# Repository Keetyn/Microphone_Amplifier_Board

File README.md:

# Microphone_Amplifier_Board

This is an audio amplifier board capable of taking any small audio signal, differential or singled ended and amplifying it to an output of 30W @ 8 ohms. This was designed, built, and tested as more of an educational exercise than anything else and thus relies on screw terminal inputs for power and requires external power supplies. This is a 4-layer board with the two inner copper layers being used as Ground planes.

The board can be thought of as having four distinct sections:

1. the first is a THAT 1510 instrumentation amplifier with a tunable gain that is meant to take in a signal       from either a microphone or an aux cord. This amplifies the signal by a gain of anywhere from +32 - +62dB      depending on the position of the gain potentiometer. This input can accept a differential or single    
   ended input.
2. The second is the EQ filter. This is a state variable topology filter. This implementation provides         
   potentiometers that allow the user to adjust the damping (alpha), Center Frequency (Fo), Gain (A), and a 
   latching pushbutton that can enable or disable the filter. Fo can be adjusted from 300Hz - 2.2kHz.             alpha can be adjusted from 0.5 - 10. Gain can be adjusted from -40dB - +15dB
3. The third is a Peak Limiter using a THAT 4305 Compander IC. This is a versatile analog processing IC that with the accompanying circuitry and potentiometers acts as a non-distorting peak limiter with the ability to adjust the compression threshold and compression ratio. The threshold can be adjusted from +7.3dBV - +9.74dBV. The compression ratio can also be adjusted anywhere from infinity:1 to a value approaching 1:1.
4. THe final section of this board is a TPA3122 Class-D analog input power amplifier. This IC is capable of outputting 30W and has an accompanying potentiometer that can be used to attenuate its input as a volume control.

Each of the above listed sections is split apart by 100 mil pin headers that completely break any connection between the sections. This was done for easier test and troubleshooting and to help compartmentalize individual portions of the board. Below is a screenshot of a 3D render of the board in KiCad with each section clearly separate with silkscreen lines and labels.

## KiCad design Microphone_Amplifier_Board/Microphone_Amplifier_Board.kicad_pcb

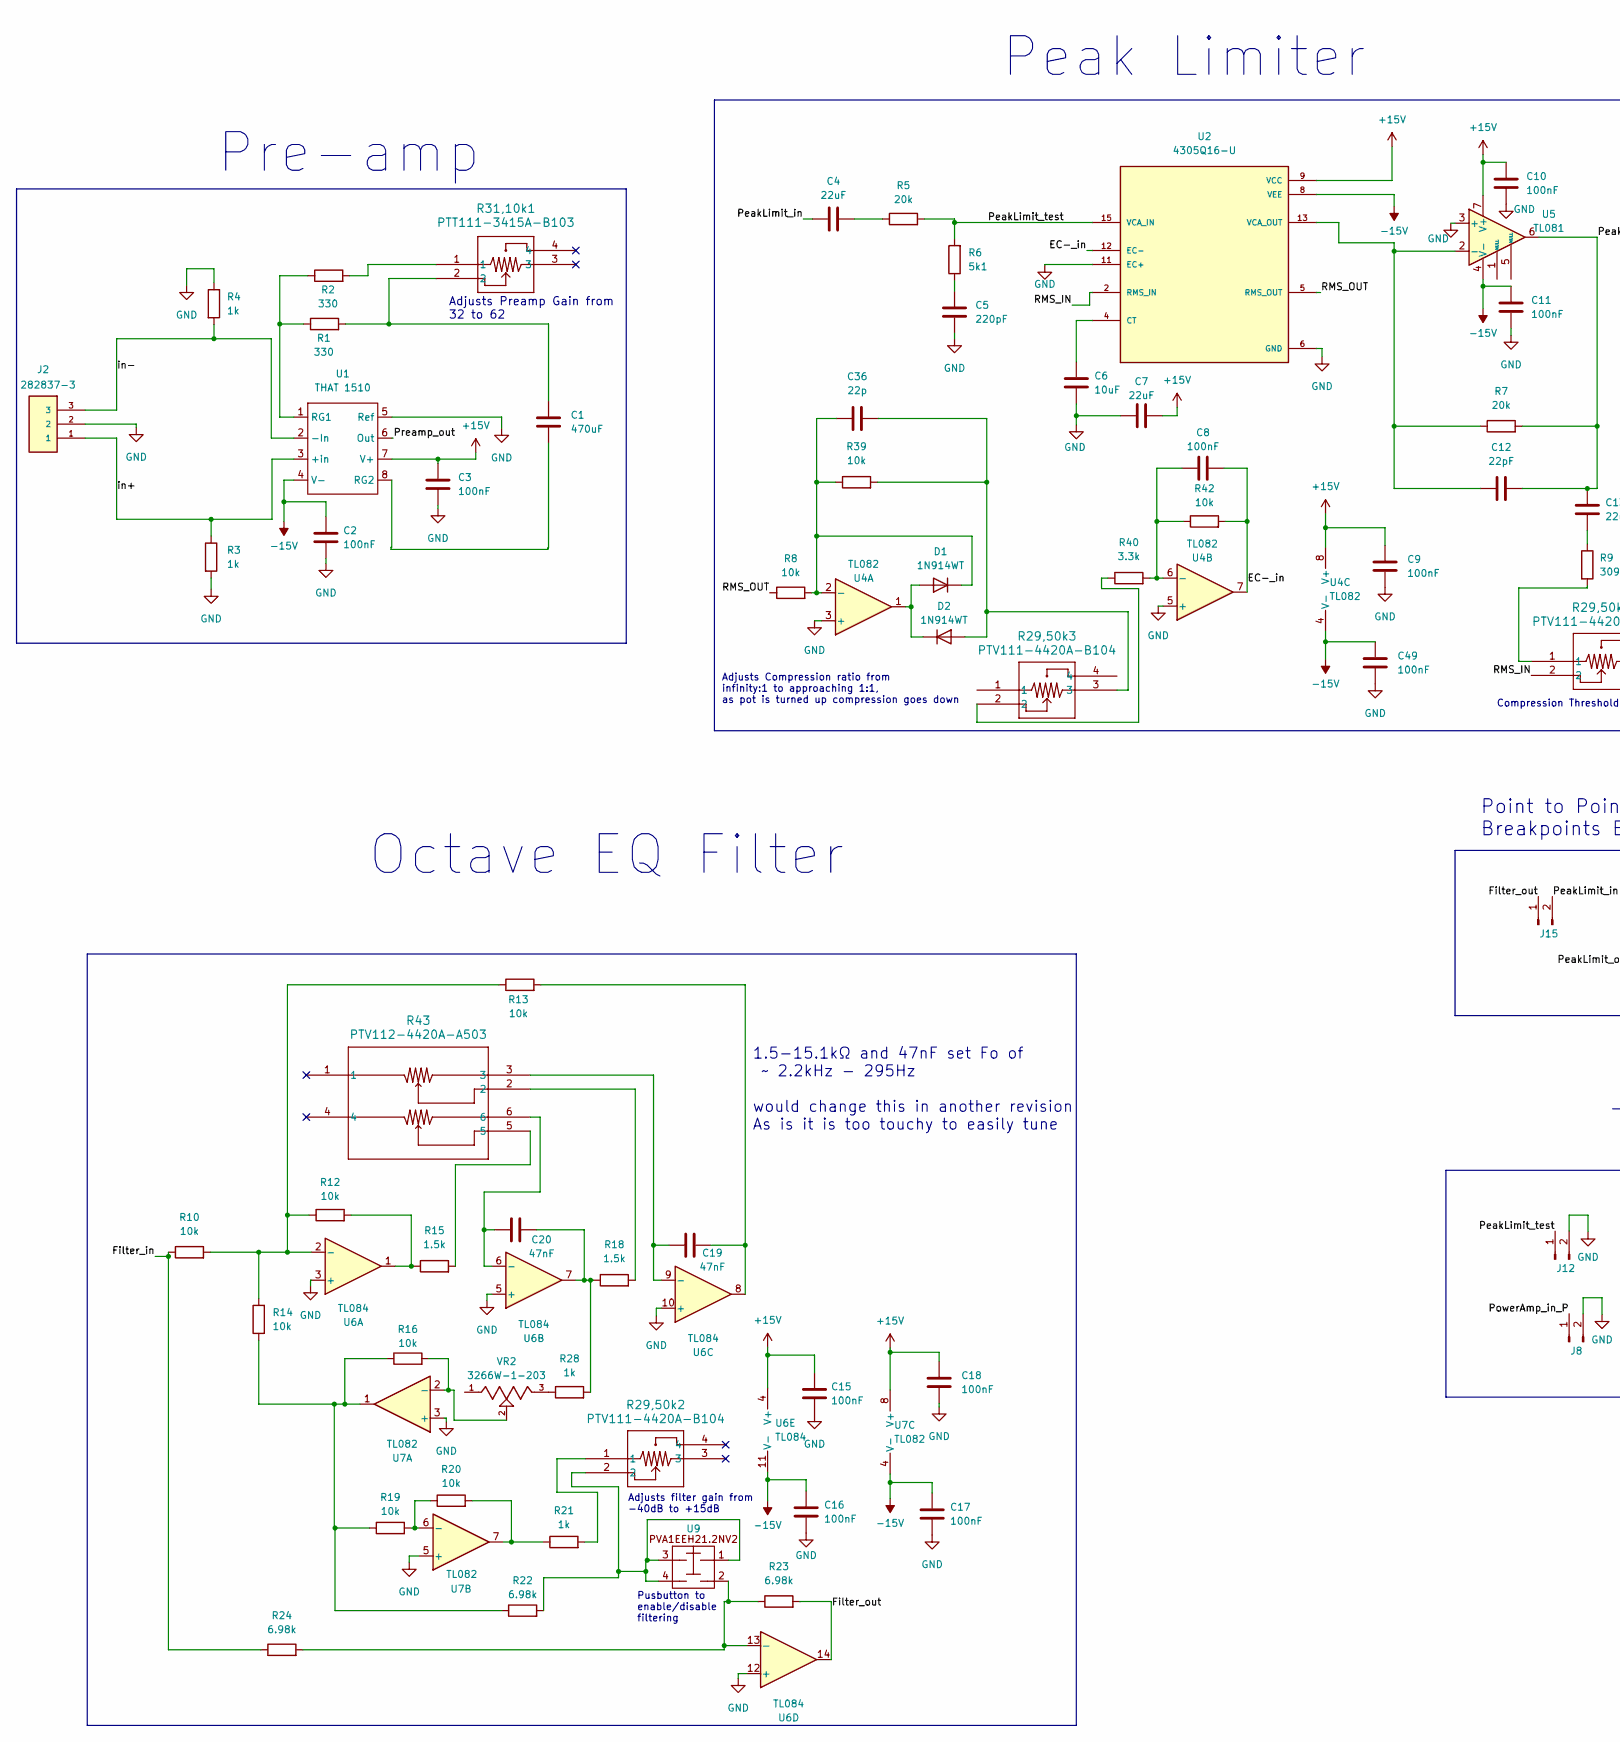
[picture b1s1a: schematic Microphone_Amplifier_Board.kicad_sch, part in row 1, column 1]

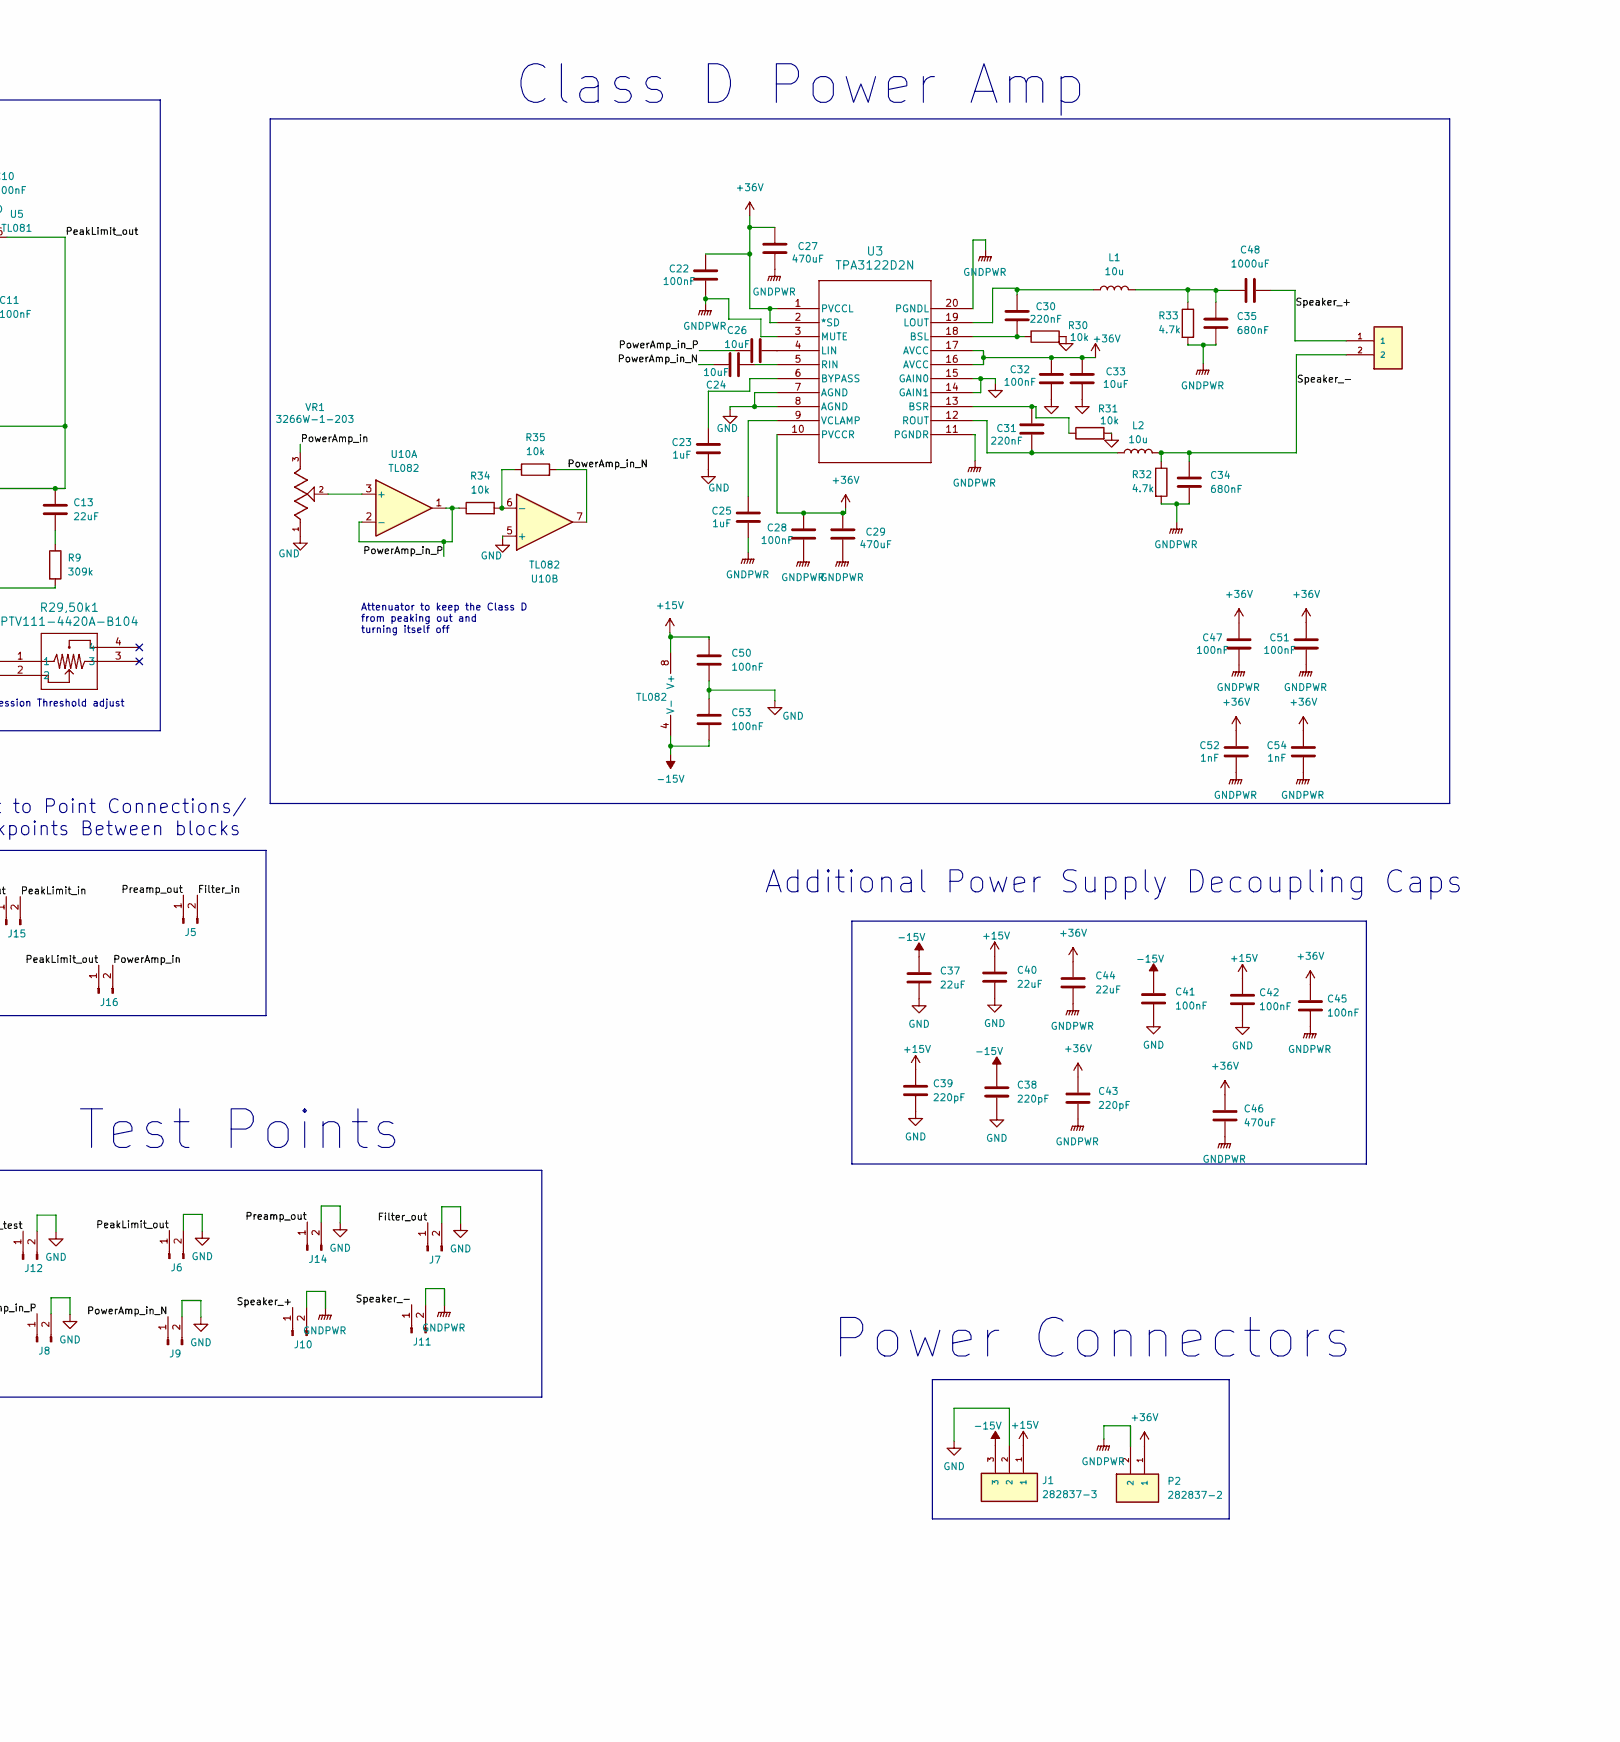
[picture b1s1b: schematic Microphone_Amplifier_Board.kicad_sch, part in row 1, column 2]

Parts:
C1, C27, C29, C46: 470uF; CP_Radial_D13.0mm_P5.00mm
C2, C3, C8, C9, C10, C11, C15, C16, C17, C18, C22, C28, C32, C41, C42, C45, C47, C49, C50, C51, C53: 100nF; C_1206_3216Metric_Pad1.33x1.80mm_HandSolder
C4, C7, C13, C37, C40, C44: 22uF; C_1206_3216Metric_Pad1.33x1.80mm_HandSolder
C5, C38, C39, C43: 220pF; C_1206_3216Metric_Pad1.33x1.80mm_HandSolder
C6, C24, C26, C33: 10uF; C_1206_3216Metric_Pad1.33x1.80mm_HandSolder
C12: 22pF; C_1206_3216Metric_Pad1.33x1.80mm_HandSolder
C19, C20: 47nF; C_1206_3216Metric_Pad1.33x1.80mm_HandSolder
C23, C25: 1uF; C_1206_3216Metric_Pad1.33x1.80mm_HandSolder
C30, C31: 220nF; C_1206_3216Metric_Pad1.33x1.80mm_HandSolder
C34, C35: 680nF; C_1206_3216Metric_Pad1.33x1.80mm_HandSolder
C36: 22p; C_1206_3216Metric_Pad1.33x1.80mm_HandSolder
C48: 1000uF; CP_Radial_D13.0mm_P5.00mm
C52, C54: 1nF; C_1206_3216Metric_Pad1.33x1.80mm_HandSolder
D1, D2: 1N914WT; D_SOD-523
J1, J2: 282837-3; TE_282837-3; PARTREV H; DigiKey_Part_Number A113321-ND
J5, J6, J7, J8, J9, J10, J11, J12, J14, J15, J16: Conn_01x02_Pin; PinHeader_1x02_P2.54mm_Vertical
L1, L2: 10u; Power Inductor 10uH
P1, P2: 282837-2; TE_282837-2; PARTREV G3; DigiKey_Part_Number A113320-ND
R1, R2: 330; R_1206_3216Metric_Pad1.30x1.75mm_HandSolder
R3, R4, R21, R28: 1k; R_1206_3216Metric_Pad1.30x1.75mm_HandSolder
R5, R7: 20k; R_1206_3216Metric_Pad1.30x1.75mm_HandSolder
R6: 5k1; R_1206_3216Metric_Pad1.30x1.75mm_HandSolder
R8, R10, R12, R13, R14, R16, R19, R20, R30, R31, R34, R35, R39, R42: 10k; R_1206_3216Metric_Pad1.30x1.75mm_HandSolder
R9: 309k; R_1206_3216Metric_Pad1.30x1.75mm_HandSolder
R15, R18: 1.5k; R_1206_3216Metric_Pad1.30x1.75mm_HandSolder
R22, R23, R24: 6.98k; R_1206_3216Metric_Pad1.30x1.75mm_HandSolder
R29,50k1, R29,50k2, R29,50k3: PTV111-4420A-B104; PTT111-3_17_BRN
R31,10k1: PTT111-3415A-B103; PTT111-3_17_BRN
R32, R33: 4.7k; R_1206_3216Metric_Pad1.30x1.75mm_HandSolder
R40: 3.3k; R_1206_3216Metric_Pad1.30x1.75mm_HandSolder
R43: PTV112-4420A-A503; PTV112-4_BRN
U1: THAT 1510
U2: 4305Q16-U; PARTREV 10
U3: TPA3122D2N; N20
U4, U7: TL082
U5: TL081
U6: TL084
U9: (no value)
U10: TL082; TL081 SOIC-8
VR1, VR2: 3266W-1-203; TRIM_3266W-1-203

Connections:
+15V: C3.1, C7.2, C9.2, C10.1, C15.1, C18.1, C39.1, C40.1, C42.1, C50.1, J1.1, U1.7 (V+), U2.9 (VCC), U4.8 (V+), U5.7 (V+), U6.4 (V+), U7.8 (V+), U10.8 (V+)
+36V: C22.1, C27.1, C28.1, C29.1, C32.1, C33.1, C43.1, C44.1, C45.1, C46.1, C47.1, C51.1, C52.1, C54.1, P2.1, U3.1 (PVCCL), U3.2 (*SD), U3.10 (PVCCR), U3.16 (AVCC), U3.17 (AVCC)
-15V: C2.1, C11.1, C16.1, C17.1, C37.1, C38.1, C41.1, C49.2, C53.2, J1.3, U1.4 (V-), U2.8 (VEE), U4.4 (V-), U5.4 (V-), U6.11 (V-), U7.4 (V-), U10.4 (V-)
/EC-_in: C8.2, R42.2, U2.12 (EC-), U4.7
/Filter_in: J5.2, R10.1, R24.1
/Filter_out: J7.1, J15.1, R23.2, U6.14
/PeakLimit_in: C4.1, J15.2
/PeakLimit_out: C12.2, C13.1, J6.1, J16.1, R7.2, U5.6
/PeakLimit_test: J12.1, R5.2, R6.2, U2.15 (VCA_IN)
/PowerAmp_in: J16.2, VR1.3
/PowerAmp_in_N: C24.2, J9.1, R35.2, U10.7
/PowerAmp_in_P: C26.2, J8.1, R34.1, U10.1, U10.2 (-)
/Preamp_out: J5.1, J14.1, U1.6 (Out)
/RMS_IN: R29,50k1.2, U2.2 (RMS_IN)
/RMS_OUT: R8.1, U2.5 (RMS_OUT)
/Speaker_+: C48.2, J10.1, P1.1
/Speaker_-: C34.1, J11.1, L2.2, P1.2, R32.1
/in+: J2.1, R3.1, U1.3 (+in)
/in-: J2.3, R4.2, U1.2 (-In)
GND: C2.2, C3.2, C5.2, C6.2, C7.1, C9.1, C10.2, C11.2, C15.2, C16.2, C17.2, C18.2, C23.2, C32.2, C33.2, C37.2, C38.2, C39.2, C40.2, C41.2, C42.2, C49.1, C50.2, C53.1, J1.2, J2.2, J6.2, J7.2, J8.2, J9.2, J12.2, J14.2, R3.2, R4.1, R30.2, R31.2, U1.5 (Ref), U2.6 (GND), U2.11 (EC+), U3.7 (AGND), U3.8 (AGND), U3.14 (GAIN1), U3.15 (GAIN0), U4.3 (+), U4.5 (+), U5.3 (+), U6.3 (+), U6.5 (+), U6.10 (+), U6.12 (+), U7.3 (+), U7.5 (+), U10.5 (+), VR1.1
GNDPWR: C22.2, C25.2, C27.2, C28.2, C29.2, C34.2, C35.2, C43.2, C44.2, C45.2, C46.2, C47.2, C51.2, C52.2, C54.2, J10.2, J11.2, P2.2, R32.2, R33.2, U3.3 (MUTE), U3.11 (PGNDR), U3.20 (PGNDL)
unnamed: C1.1, R1.2, R31,10k1.2
unnamed: C4.2, R5.1
unnamed: C5.1, R6.1
unnamed: C13.2, R9.1
unnamed: C19.2, R13.2, U6.8
unnamed: C20.2, R18.1, R28.2, U6.7
unnamed: C35.1, C48.1, L1.2, R33.1
unnamed: D1.2 (A), D2.1 (K), U4.1
unnamed: C36.1, D1.1 (K), R8.2, R39.1, U4.2 (-)
unnamed: C36.2, D2.2 (A), R29,50k3.3, R39.2
unnamed: R2.2, R31,10k1.1
unnamed: R12.2, R15.1, U6.1
unnamed: R14.1, R16.1, R19.1, R22.1, U7.1
unnamed: R15.2, R43.5
unnamed: R18.2, R43.2
unnamed: R20.2, R21.1, U7.7
unnamed: R21.2, R29,50k2.1
unnamed: R22.2, R29,50k2.2, U9.1, U9.3, U9.4
unnamed: R28.1, VR2.3
unnamed: R9.2, R29,50k1.1
unnamed: R29,50k3.2, R40.1
unnamed: R1.1, R2.1, U1.1 (RG1)
unnamed: C1.2, U1.8 (RG2)
unnamed: C6.1, U2.4 (CT)
unnamed: C12.1, R7.1, U2.13 (VCA_OUT), U5.2 (-)
unnamed: C30.2, R30.1, U3.18 (BSL)
unnamed: C31.1, R31.1, U3.13 (BSR)
unnamed: C23.1, U3.6 (BYPASS)
unnamed: C26.1, U3.4 (LIN)
unnamed: C30.1, L1.1, U3.19 (LOUT)
unnamed: C24.1, U3.5 (RIN)
unnamed: C31.2, L2.1, U3.12 (ROUT)
unnamed: C25.1, U3.9 (VCLAMP)
unnamed: C8.1, R40.2, R42.1, U4.6 (-)
unnamed: R10.2, R12.1, R13.1, R14.2, U6.2 (-)
unnamed: C20.1, R43.6, U6.6 (-)
unnamed: C19.1, R43.3, U6.9 (-)
unnamed: R23.1, R24.2, U6.13 (-), U9.2
unnamed: R16.2, U7.2 (-), VR2.2
unnamed: R19.2, R20.1, U7.6 (-)
unnamed: U10.3 (+), VR1.2
unnamed: R34.2, R35.1, U10.6 (-)

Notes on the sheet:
Pusbutton to enable/disable filtering
Compression Threshold adjust
Adjusts filter gain from -40dB to +15dB
Test Points
Peak Limiter
Class D Power Amp
Power Connectors
Additional Power Supply Decoupling Caps
Octave EQ Filter
Attenuator to keep the Class D from peaking out and turning itself off
Point to Point Connections/ Breakpoints Between blocks
Adjusts Compression ratio from infinity:1 to approaching 1:1, as pot is turned up compression goes down
1.5-15.1kΩ and 47nF set Fo of ~ 2.2kHz - 295Hz would change this in another revision As is it is too touchy to easily tune
Adjusts Preamp Gain from 32 to 62
Pre-amp

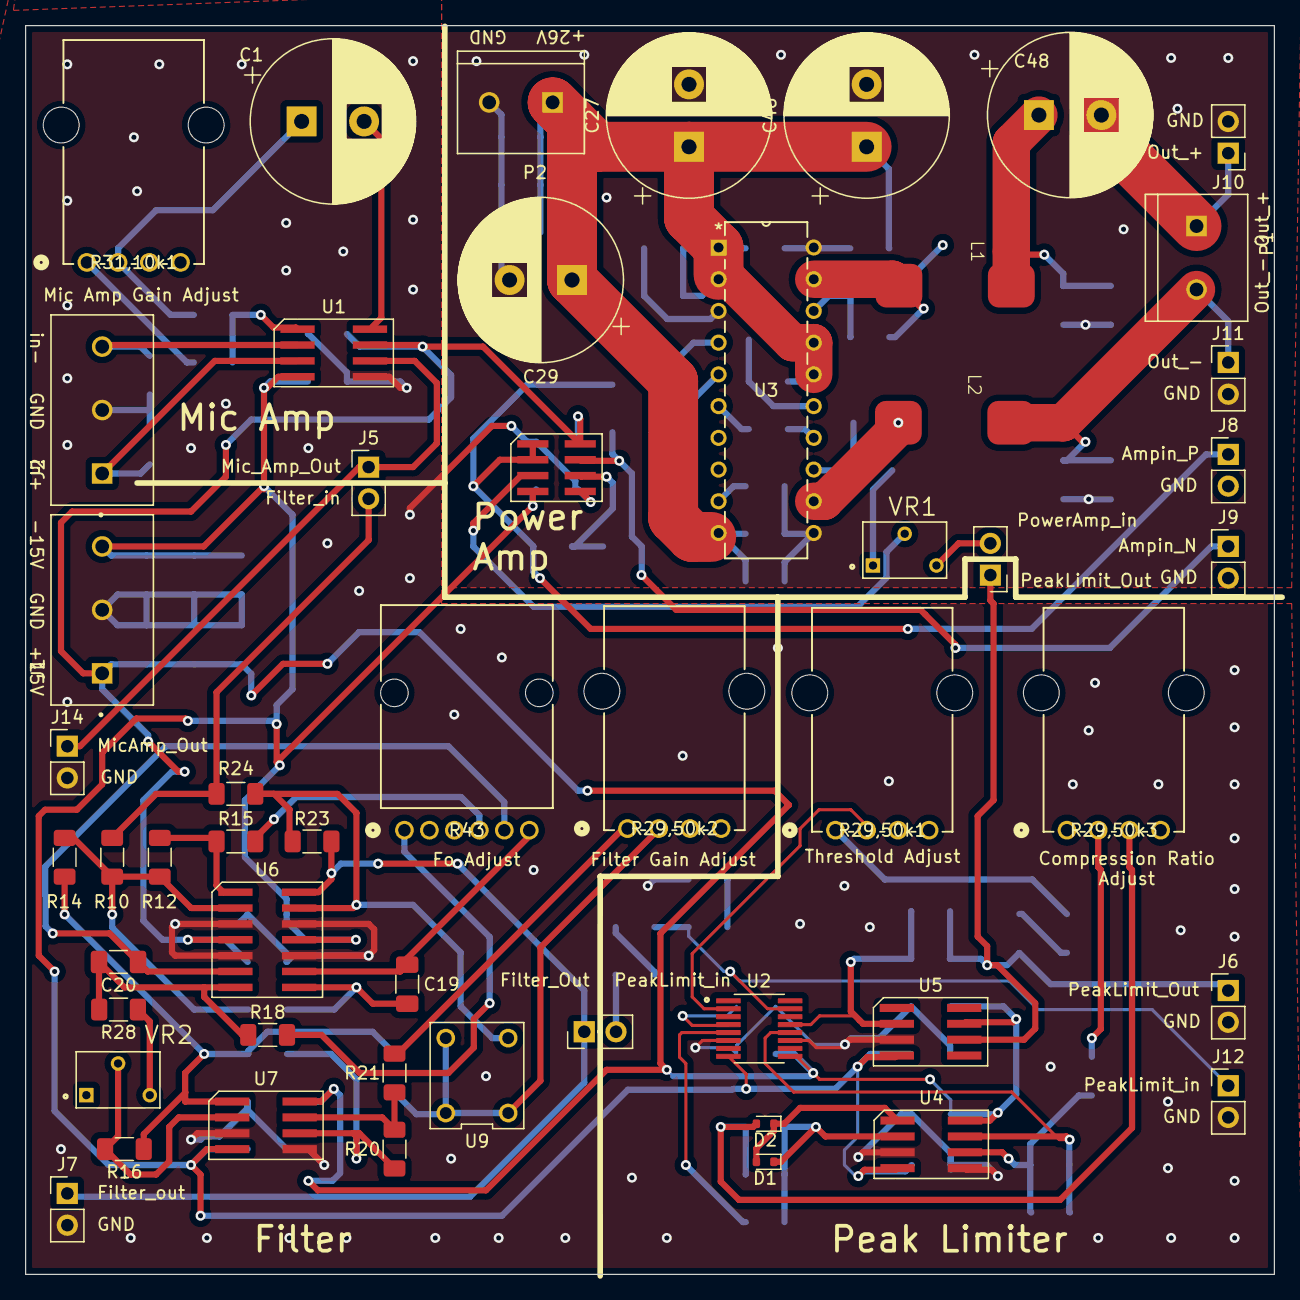
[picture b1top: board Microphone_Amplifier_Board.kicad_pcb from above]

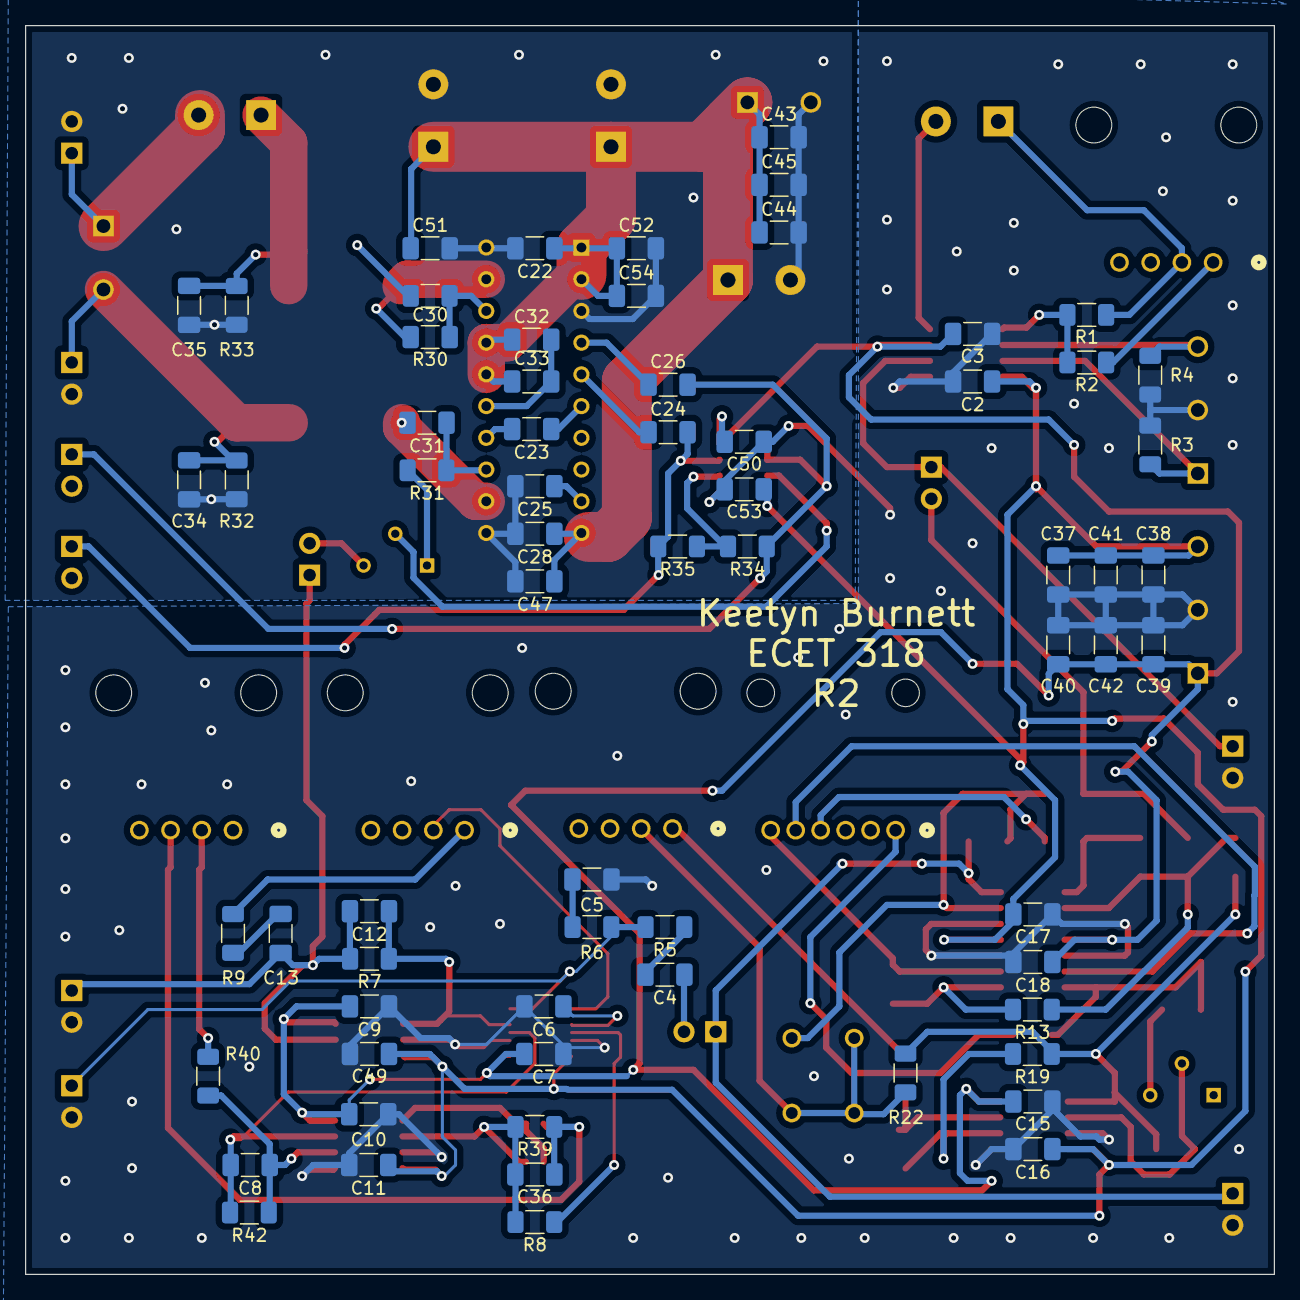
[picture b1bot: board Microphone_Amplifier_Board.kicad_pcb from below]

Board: 4 copper layers, 100.0 x 100.0 mm, 119 parts (66 on the bottom side), 63 nets.

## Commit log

2024-09-16 Adding Complete Project to Github
2024-09-16 Adding Images for Readme
